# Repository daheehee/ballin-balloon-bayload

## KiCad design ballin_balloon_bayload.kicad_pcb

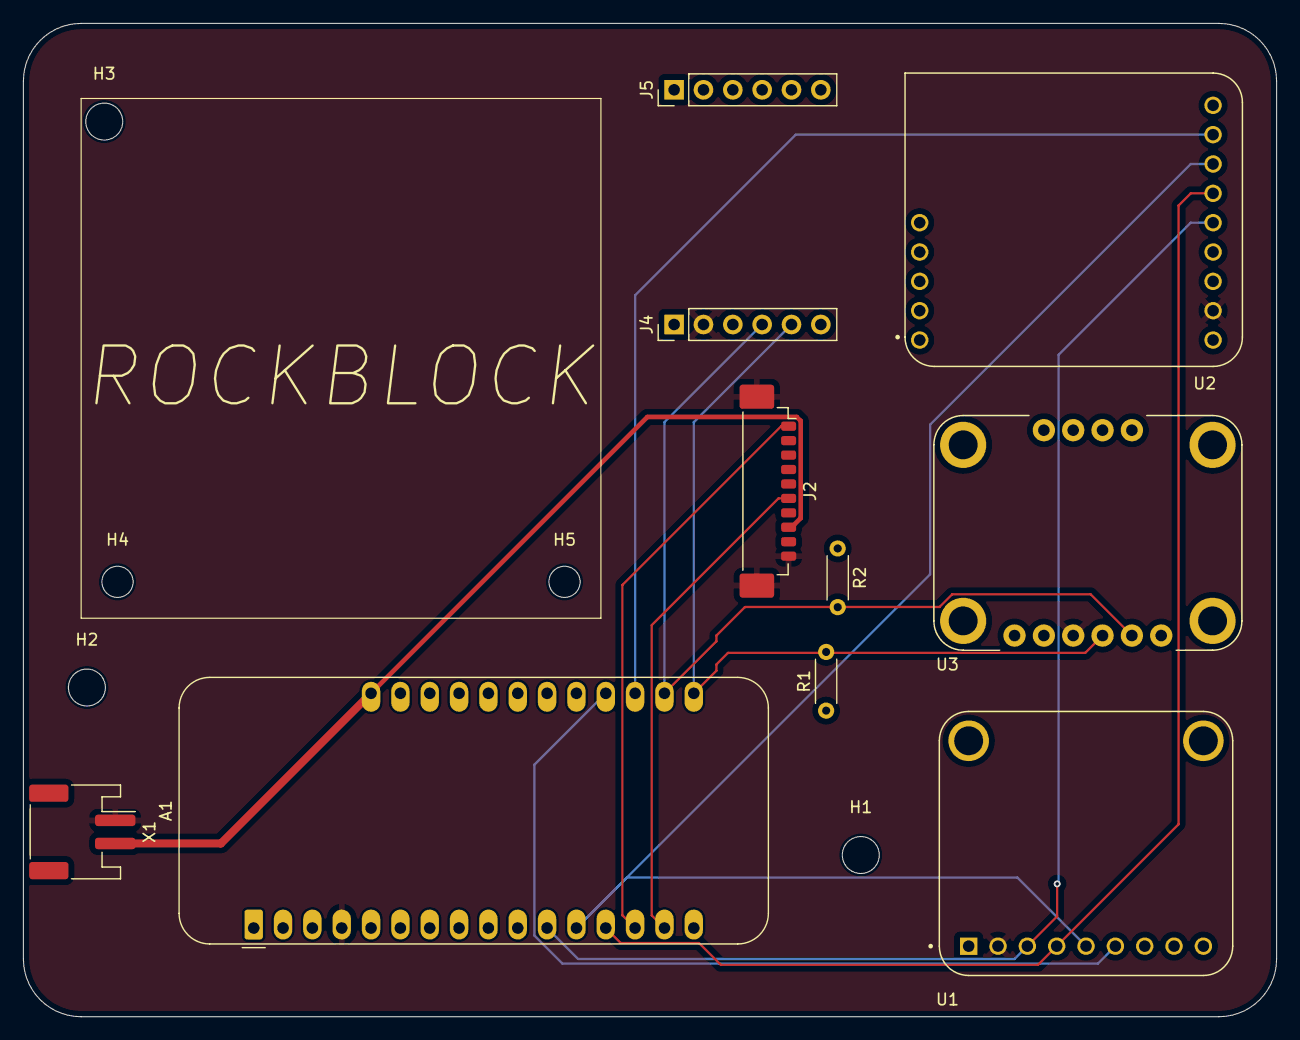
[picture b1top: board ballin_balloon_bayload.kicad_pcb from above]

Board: 4 copper layers, 108.5 x 86.0 mm, 15 parts (0 on the bottom side), 12 nets.

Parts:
A1: Adafruit_Feather_HUZZAH32_ESP32; Adafruit_Feather
H1, H2, H3: MountingHole; MountingHole_3.2mm_M3
H4, H5: MountingHole; MountingHole_2.7mm_M2.5
J2: Molex 0532611071; Molex_PicoBlade_53398-1071_1x10-1MP_P1.25mm_Vertical
J4, J5: Conn_01x06_Pin; PinHeader_1x06_P2.54mm_Vertical
R1, R2: 10k; R_Axial_DIN0204_L3.6mm_D1.6mm_P5.08mm_Horizontal
U1: MICROSD_SPI_OR_SDIO_CARD; MODULE_MICROSD_SPI_OR_SDIO_CARD
U2: 3073; Adafruit_RFM96W_LoRa_Radio_3073
U3: 2472; adafruit_IMU_2472
X1: JST_PH_S2B-PH-SM4-TB_1x02-1MP_P2.00mm_Horizontal

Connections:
+3V3: A1.2 (3V3), J4.1, R1.1, R2.1, U1.1 (3V), U2.JP3_1 (VIN), U3.1 (VIN)
+5V: A1.28 (VBAT), J2.8, X1.2
/inside/CS_LoRa: A1.19 (A6/IO14), U2.JP3_8 (~CS)
/inside/CS_microSD: A1.20 (A7/IO32), U1.6 (D3/CS)
/inside/MISO: A1.13 (MISO/IO19), U1.4 (D0/SO), U2.JP3_6 (MISO)
/inside/MOSI: A1.12 (MOSI/IO18), U1.5 (CMD/SI), U2.JP3_7 (MOSI)
/inside/RX_MCU: A1.14 (RX/IO16), J2.1
/inside/SCK: A1.11 (SCK/IO5), U1.3 (CLK), U2.JP3_5 (SCK)
/inside/SCL: A1.18 (SCL/IO22), J4.4, R2.2, U3.5 (SCL)
/inside/SDA: A1.17 (SDA/IO23), J4.5, R1.2, U3.4 (SDA)
/inside/TX_MCU: A1.15 (TX/IO17), J2.6
GND: A1.4 (GND), J2.10, J2.MP (MountPin), J4.2, U1.2 (GND), U2.JP3_2 (GND), U3.3 (GND), X1.1

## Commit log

2025-07-28 starting
2025-07-28 added footprints
2025-07-29 Update schematic and PCB
2025-07-29 updated footprints
2025-07-29 added molex 0532 footprint
2025-07-30 Rough draft of files for component wise PCB
2025-07-30 I had to reset my branch because something was pushed incorrectly and none of the schematic files were working
2025-07-31 more stuff?
2025-07-31 Version 1.0 of Compiled PCB
2025-08-02 updated pcb layout
2025-08-02 verifying connections before pcb creation
2025-08-06 v1.0 with LTC1628 switcher
2025-08-14 esp32-s3-wroom1u version
2025-09-29 "finished breakout version"
2025-10-01 small tweaks
2025-10-17 sorry actual update
